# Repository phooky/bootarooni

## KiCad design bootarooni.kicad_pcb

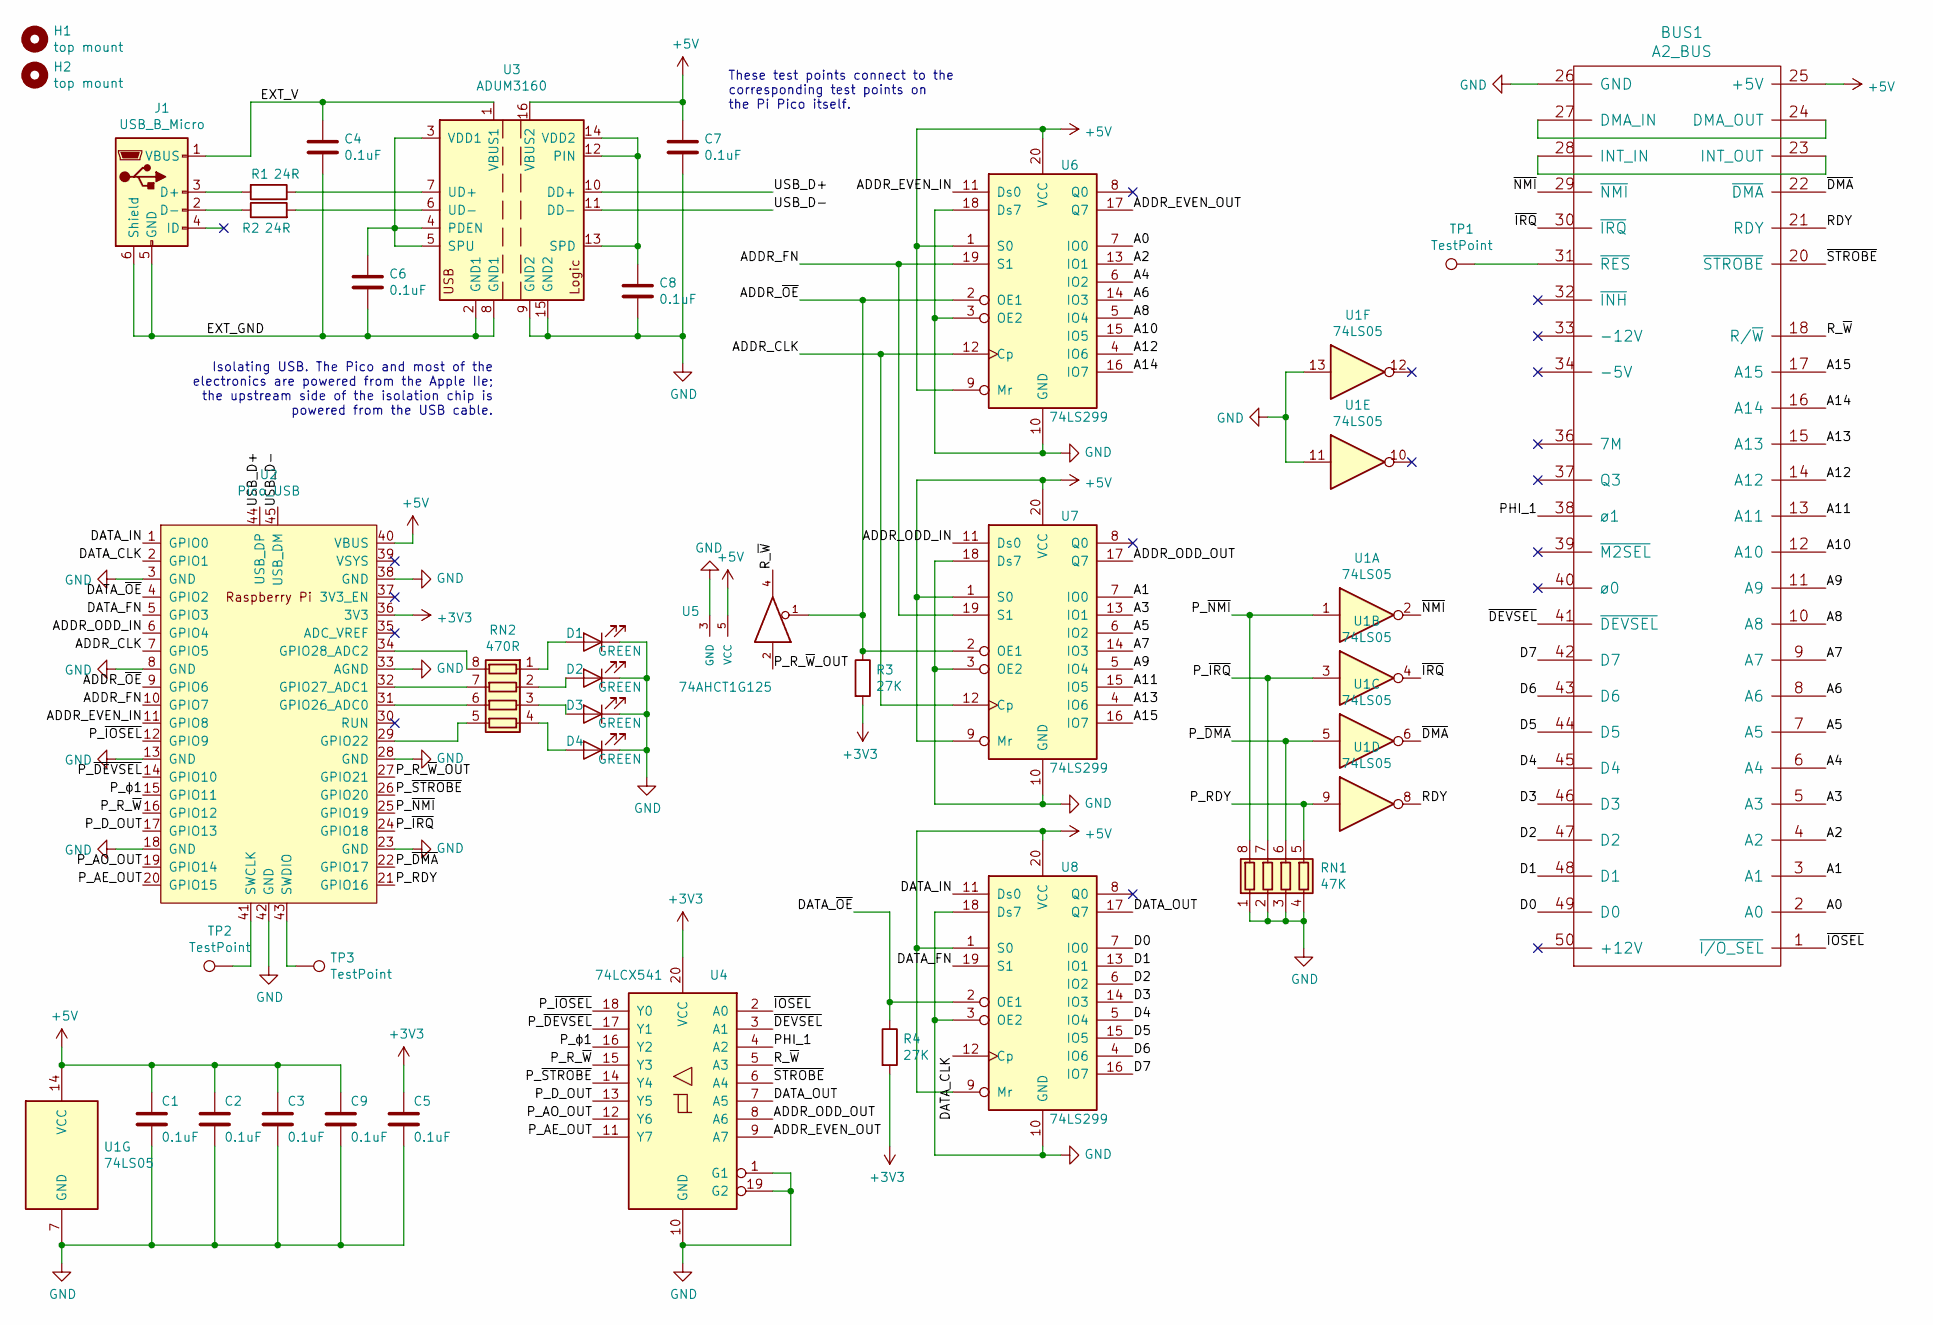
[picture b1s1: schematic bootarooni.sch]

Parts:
BUS1: A2_BUS; BUS_A2
C1, C2, C3, C4, C5, C6, C7, C8, C9: 0.1uF; C_0805_2012Metric; Digikey P/N 399-8000-1-ND
D1, D2, D3, D4: GREEN; LED_0805_2012Metric; Digikey P/N 160-1423-1-ND
H1, H2: top mount; MountingHole_3.2mm_M3
J1: USB_B_Micro; USB_Micro-B_Amphenol_10103594-0001LF_Horizontal; Digikey P/N 609-4050-1-ND
R1, R2: 24R; R_0805_2012Metric; Digikey P/N P24.0CCT-ND
R3, R4: 27K; R_0805_2012Metric; Digikey P/N P27.0KCCT-ND
RN1: 47K; SOIC-8; Digikey P/N Y10473CT-ND
RN2: 470R; SOIC-8; Digikey P/N Y7471CT-ND
TP1: TestPoint; TestPoint_Pad_D2.0mm
TP2, TP3: TestPoint; TestPoint_Pad_D1.5mm
U1: 74LS05; SOIC-14_3.9x8.7mm_P1.27mm; Digikey P/N 296-1630-1-ND
U2: Pico_USB; RPi_Pico_USB_SMD_TH
U3: ADUM3160; SOIC-16W_7.5x10.3mm_P1.27mm; Digikey P/N ADUM3160BRWZ-RLCT-ND
U4: 74LCX541; SOIC-20W_7.5x12.8mm_P1.27mm; Digikey P/N 74LCX541WMXCT-ND
U5: 74AHCT1G125; SOT-353_SC-70-5; Digikey P/N M74VHC1GT125DF1GOSCT-ND
U6, U7, U8: 74LS299; SOIC-20W_7.5x12.8mm_P1.27mm; Digikey P/N 296-4277-5-ND

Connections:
+3V3: C5.2, R3.2, R4.2, U2.36 (3V3), U4.20 (VCC)
+5V: BUS1.25 (+5V), C1.2, C2.2, C3.2, C7.1, C9.2, U1.14 (VCC), U2.40 (VBUS), U3.16 (VBUS2), U5.5 (VCC), U6.1 (S0), U6.9 (Mr), U6.20 (VCC), U7.1 (S0), U7.9 (Mr), U7.20 (VCC), U8.1 (S0), U8.9 (Mr), U8.20 (VCC)
/A0: BUS1.2 (A0), U6.7 (IO0)
/A1: BUS1.3 (A1), U7.7 (IO0)
/A2: BUS1.4 (A2), U6.13 (IO1)
/A3: BUS1.5 (A3), U7.13 (IO1)
/A4: BUS1.6 (A4), U6.6 (IO2)
/A5: BUS1.7 (A5), U7.6 (IO2)
/A6: BUS1.8 (A6), U6.14 (IO3)
/A7: BUS1.9 (A7), U7.14 (IO3)
/A8: BUS1.10 (A8), U6.5 (IO4)
/A9: BUS1.11 (A9), U7.5 (IO4)
/A10: BUS1.12 (A10), U6.15 (IO5)
/A11: BUS1.13 (A11), U7.15 (IO5)
/A12: BUS1.14 (A12), U6.4 (IO6)
/A13: BUS1.15 (A13), U7.4 (IO6)
/A14: BUS1.16 (A14), U6.16 (IO7)
/A15: BUS1.17 (A15), U7.16 (IO7)
/ADDR_CLK: U2.7 (GPIO5), U6.12 (Cp), U7.12 (Cp)
/ADDR_EVEN_IN: U2.11 (GPIO8), U6.11 (Ds0)
/ADDR_EVEN_OUT: U4.9 (A7), U6.17 (Q7)
/ADDR_FN: U2.10 (GPIO7), U6.19 (S1), U7.19 (S1)
/ADDR_ODD_IN: U2.6 (GPIO4), U7.11 (Ds0)
/ADDR_ODD_OUT: U4.8 (A6), U7.17 (Q7)
/ADDR_~OE~: R3.1, U2.9 (GPIO6), U5.1, U6.2 (OE1), U7.2 (OE1)
/D0: BUS1.49 (D0), U8.7 (IO0)
/D1: BUS1.48 (D1), U8.13 (IO1)
/D2: BUS1.47 (D2), U8.6 (IO2)
/D3: BUS1.46 (D3), U8.14 (IO3)
/D4: BUS1.45 (D4), U8.5 (IO4)
/D5: BUS1.44 (D5), U8.15 (IO5)
/D6: BUS1.43 (D6), U8.4 (IO6)
/D7: BUS1.42 (D7), U8.16 (IO7)
/DATA_CLK: U2.2 (GPIO1), U8.12 (Cp)
/DATA_FN: U2.5 (GPIO3), U8.19 (S1)
/DATA_IN: U2.1 (GPIO0), U8.11 (Ds0)
/DATA_OUT: U4.7 (A5), U8.17 (Q7)
/DATA_~OE~: R4.1, U2.4 (GPIO2), U8.2 (OE1)
/EXT_GND: C4.2, C6.2, J1.5 (GND), J1.6 (Shield), U3.2 (GND1), U3.8 (GND1)
/EXT_V: C4.1, J1.1 (VBUS), U3.1 (VBUS1)
/PHI_1: BUS1.38 (ø1), U4.4 (A2)
/P_AE_OUT: U2.20 (GPIO15), U4.11 (Y7)
/P_AO_OUT: U2.19 (GPIO14), U4.12 (Y6)
/P_D_OUT: U2.17 (GPIO13), U4.13 (Y5)
/P_RDY: RN1.5 (R4.2), U1.9, U2.21 (GPIO16)
/P_R_~W~: U2.16 (GPIO12), U4.15 (Y3)
/P_R_~W~_OUT: U2.27 (GPIO21), U5.2
/P_~DEVSEL~: U2.14 (GPIO10), U4.17 (Y1)
/P_~DMA~: RN1.6 (R3.2), U1.5, U2.22 (GPIO17)
/P_~IOSEL~: U2.12 (GPIO9), U4.18 (Y0)
/P_~IRQ~: RN1.7 (R2.2), U1.3, U2.24 (GPIO18)
/P_~NMI~: RN1.8 (R1.2), U1.1, U2.25 (GPIO19)
/P_~STROBE~: U2.26 (GPIO20), U4.14 (Y4)
/P_ϕ1: U2.15 (GPIO11), U4.16 (Y2)
/RDY: BUS1.21 (RDY), U1.8
/R_~W~: BUS1.18 (R/~W), U4.5 (A3), U5.4
/USB_D+: U2.44 (USB_DP), U3.10 (DD+)
/USB_D-: U2.45 (USB_DM), U3.11 (DD-)
/~DEVSEL~: BUS1.41 (~DEVSEL), U4.3 (A1)
/~DMA~: BUS1.22 (~DMA), U1.6
/~IOSEL~: BUS1.1 (~I/O_SEL), U4.2 (A0)
/~IRQ~: BUS1.30 (~IRQ), U1.4
/~NMI~: BUS1.29 (~NMI), U1.2
/~STROBE~: BUS1.20 (~STROBE), U4.6 (A4)
GND: BUS1.26 (GND), C1.1, C2.1, C3.1, C5.1, C7.2, C8.2, C9.1, D1.1 (K), D2.1 (K), D3.1 (K), D4.1 (K), RN1.1 (R1.1), RN1.2 (R2.1), RN1.3 (R3.1), RN1.4 (R4.1), U1.7 (GND), U1.11, U1.13, U2.3 (GND), U2.8 (GND), U2.13 (GND), U2.18 (GND), U2.23 (GND), U2.28 (GND), U2.33 (AGND), U2.38 (GND), U2.42 (GND), U3.9 (GND2), U3.15 (GND2), U4.1 (G1), U4.10 (GND), U4.19 (G2), U5.3 (GND), U6.3 (OE2), U6.10 (GND), U6.18 (Ds7), U7.3 (OE2), U7.10 (GND), U7.18 (Ds7), U8.3 (OE2), U8.10 (GND), U8.18 (Ds7)
unnamed: BUS1.23 (INT_OUT), BUS1.28 (INT_IN)
unnamed: BUS1.24 (DMA_OUT), BUS1.27 (DMA_IN)
unnamed: BUS1.31 (~RES), TP1.1
unnamed: C6.1, U3.3 (VDD1), U3.4 (PDEN), U3.5 (SPU)
unnamed: C8.1, U3.12 (PIN), U3.13 (SPD), U3.14 (VDD2)
unnamed: D1.2 (A), RN2.1 (R1.1)
unnamed: D2.2 (A), RN2.2 (R2.1)
unnamed: D3.2 (A), RN2.3 (R3.1)
unnamed: D4.2 (A), RN2.4 (R4.1)
unnamed: J1.2 (D-), R2.1
unnamed: J1.3 (D+), R1.2
unnamed: R1.1, U3.7 (UD+)
unnamed: R2.2, U3.6 (UD-)
unnamed: RN2.5 (R4.2), U2.29 (GPIO22)
unnamed: RN2.6 (R3.2), U2.31 (GPIO26_ADC0)
unnamed: RN2.7 (R2.2), U2.32 (GPIO27_ADC1)
unnamed: RN2.8 (R1.2), U2.34 (GPIO28_ADC2)
unnamed: TP2.1, U2.41 (SWCLK)
unnamed: TP3.1, U2.43 (SWDIO)

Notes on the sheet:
Isolating USB. The Pico and most of the electronics are powered from the Apple IIe; the upstream side of the isolation chip is powered from the USB cable.
These test points connect to the corresponding test points on the Pi Pico itself.

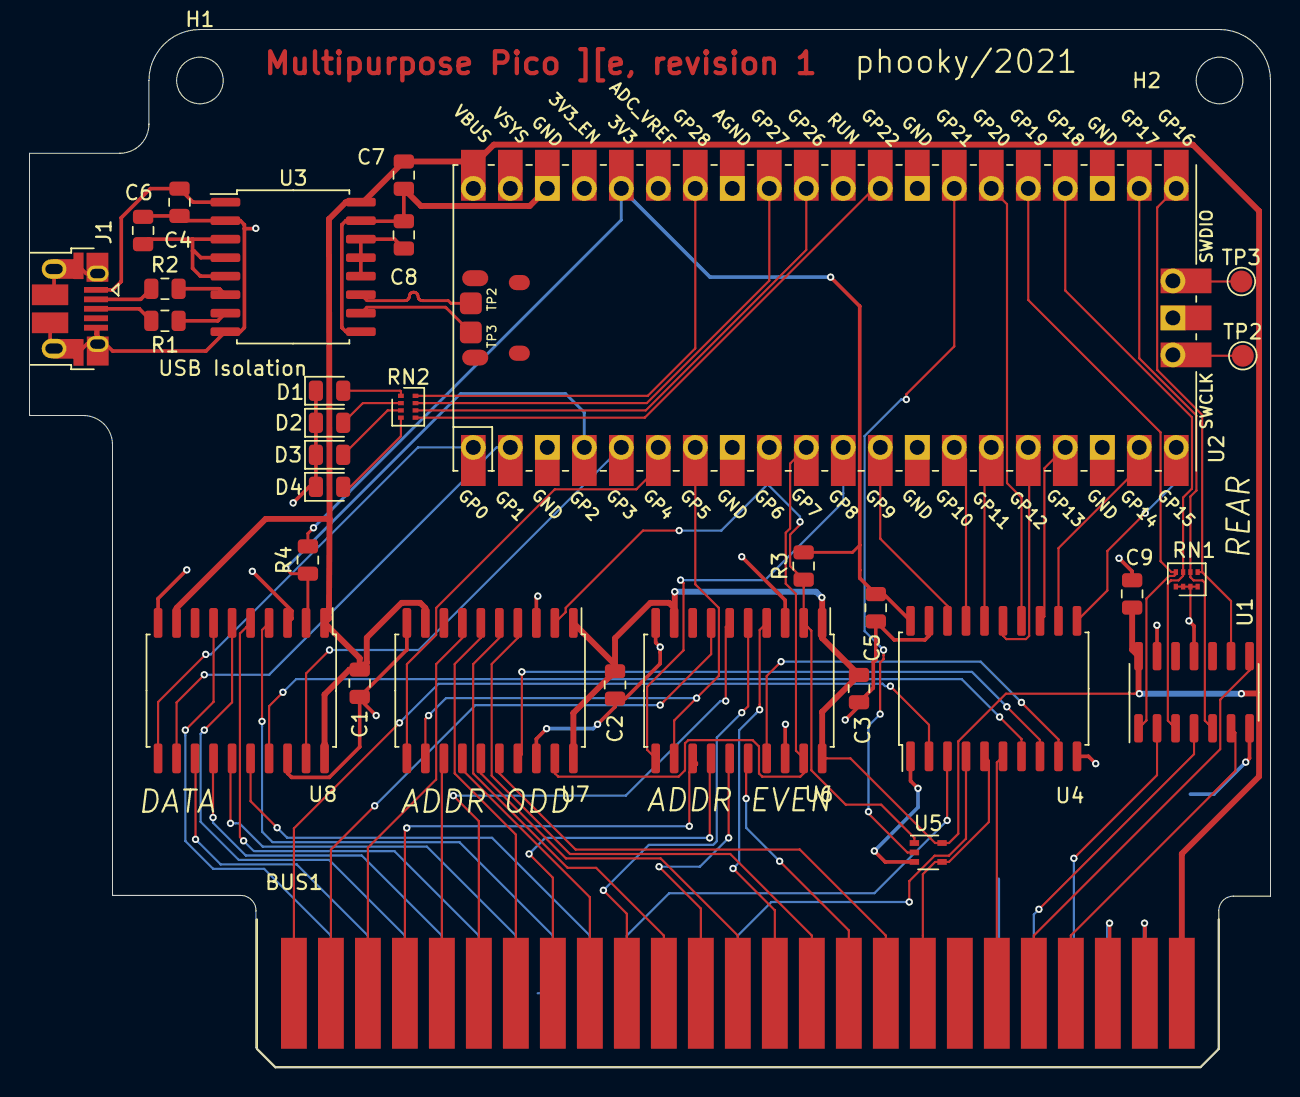
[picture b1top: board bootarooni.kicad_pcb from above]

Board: 2 copper layers, 85.2 x 71.2 mm, 34 parts (1 on the bottom side), 84 nets.

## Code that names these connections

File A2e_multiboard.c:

#include <stdio.h>
#include "pico/stdlib.h"
#include "pico/multicore.h"
#include "pico/bootrom.h"
#include "a2ebus.pio.h"

#define ARRLEN(arr) (sizeof(arr)/sizeof(arr[0]))

typedef uint pin_t;

enum {
    PIN_DATA_IN  = 0,
    PIN_DATA_CLK = 1,
    PIN_DATA_OE  = 2,
    PIN_DATA_FN  = 3,
    PIN_ADDR_ODD_IN  = 4,
    PIN_ADDR_CLK = 5,
    PIN_ADDR_OE  = 6,
    PIN_ADDR_FN  = 7,
    PIN_ADDR_EVEN_IN = 8,
    PIN_IOSEL  = 9,

    PIN_DEVSEL = 10,
    PIN_PHI1   = 11,
    PIN_RW_IN  = 12,
    PIN_DATA_OUT     = 13,
    PIN_ADDR_ODD_OUT  = 14,
    PIN_ADDR_EVEN_OUT = 15,

    PIN_RDY = 16,
    PIN_DMA = 17,
    PIN_IRQ = 18,
    PIN_NMI = 19,

    PIN_STROBE = 20,
    PIN_RW_OUT = 21,
    PIN_LED_0  = 22,
    PIN_LED_1  = 26,
    PIN_LED_2  = 27,
    PIN_LED_3  = 28,
};

const pin_t LED_PINS[] = {
    PIN_LED_0,
    PIN_LED_1,
    PIN_LED_2,
    PIN_LED_3,
};

const size_t LED_PINS_COUNT = ARRLEN(LED_PINS);

/// Initialize a GPIO pin as an output with the given level.
static inline void init_pin(pin_t pin, uint value) {
    gpio_init(pin); 
    gpio_set_dir(pin, GPIO_OUT);
    gpio_put(pin, value);
}

void initialize_gpio() {
    // These pins need to be set immediately; floating or incorrect values
    // will prevent the Apple IIe from booting.
    init_pin(PIN_ADDR_OE,1);
    init_pin(PIN_DATA_OE,1);
    init_pin(PIN_RDY,0);
    init_pin(PIN_DMA,0);
    init_pin(PIN_IRQ,0);
    init_pin(PIN_NMI,0);
    // Set up LED pins.
    init_pin(PIN_LED_0,0);
    init_pin(PIN_LED_1,0);
    init_pin(PIN_LED_2,0);
    init_pin(PIN_LED_3,0);
}

void core1() {
    PIO pio = pio0;
    uint sm = 0;
    uint offset = pio_add_program(pio, &addrbus_program);
    io_ro_32 *addr = &pio->rxf[sm];
    init_addrbus(pio, sm, offset);
    while (true) {
        while (pio_sm_is_rx_fifo_empty(pio, sm))
            tight_loop_contents();
        multicore_fifo_push_blocking(*addr);
    }

}

int main()
{
    stdio_init_all();
    initialize_gpio();
    puts("Hello, world!");
    multicore_launch_core1(core1);
    while (true) {
        int c = getchar_timeout_us(2);
        if (c == PICO_ERROR_TIMEOUT) {
            if (multicore_fifo_rvalid()) {
                uint32_t raw = multicore_fifo_pop_blocking();
                uint16_t addr = raw >> 16;
                //if (raw > 0xc000) 
                    printf("Access to address %x\n",raw);
            }
        } else if (c >= '0' && c <= '9') {
            c -= '0';
        } else if (c >= 'a' && c <= 'f') {
            c -= 'a' - 10;
        } else if (c == 'R') {
            c = -1;
            reset_usb_boot(0,0);
        } else {
            printf("Unrecognized hex digit.\n");
            c = -1; 
        }
        if (c >= 0) {
            printf("Setting LEDs to %x.\n",c);
            for (size_t i = 0; i < LED_PINS_COUNT; i++) {
                gpio_put(LED_PINS[i], (c & (1<<i))?1:0);
            }
        }
    }
    return 0;
}

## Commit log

2021-02-26 Initial bootarooni board commit
2021-02-26 adding footprints and zeroing in on component values
2021-02-26 fixing up voltage dividers for pull-up footprints for most parts
2021-03-01 Adding some NCs on schematic Rough layout on board
2021-03-01 checking in custom footprint for resistor package
2021-03-06 added LEDs, most layout done, need to reroute the power line
2021-03-07 initial layout done, needs board edge and mounting holes, along with verification
2021-03-07 added mounting holes, board outlines
2021-03-08 final v1; board, digikey, and stencil orders submitted
2021-03-21 initial checkin
2021-03-21 inline static -> static inline, as was the style at the time
2021-03-21 * initial multicore * adding hex digit parsing on core0
2021-03-21 * set LEDs from core0->core1 via fifo
2021-03-22 adding terminal code to reset into bootsel/programming mode
2021-03-22 breaking out gpio initialization
2021-03-22 paring down gpio init to prep for PIO init
2021-03-23 adding PIO code
2021-03-23 initial pass at PIO code and integration. Haven't been brave enough to switch it on yet.
2021-03-24 update part numbers to 74ACT299
2021-03-24 fixed timing, removed opt on side set, documented pio code
2021-03-24 first attempt at actual access detection
2021-03-24 well, getting *something* off the address lines.
2021-03-25 * wait for phi1 to drop before checking DEVSEL * playing with shift register timings * getting results, although need to bit swizzle
2021-03-25 swizzle bits
2021-03-26 reorganizing tree
2021-03-26 neaten up addr program comments
2021-03-26 starting in on data bus; IRQ working but not getting data yet
2021-03-29 noodled around a bit until I could get a databus read, too. TODO: figure out why i'm getting two bus accesses for a poke
2021-03-30 data <-> cpu working
2021-04-02 pare down timing for address reads
2021-04-02 attemping pin read from core1
2021-04-03 soldiering along, finally getting rw bits correctly
2021-04-12 adding flashing script, approaching working data
2021-04-12 well, at least we're currently pushing a whole byte to the data bus, even if it's backwards
2021-04-14 about as far as I'm likely to get with the current model, time to merge and branch anew
2021-04-14 some clarification in the comments
2021-04-15 refactor: always read address
2021-04-16 disable data bus
2021-04-16 proper reporting for IOSEL, DEVSEL
2021-04-16 Our pipelines were jamming our pipelines! We can now access both IOSEL and DEVSEL properly.
2021-04-17 breaking data bus read/write into seperate PIO programs
2021-04-17 messing around with timings to try to get the data bus right
2021-04-20 cleaning up and starting in on real cycle hacking
2021-04-20 adding timings; realizing that this thing is not fast enough to do what we thought it could...
2021-04-21 fix comments
2021-04-21 paring down the number of cycles needed for R/W, slowly
